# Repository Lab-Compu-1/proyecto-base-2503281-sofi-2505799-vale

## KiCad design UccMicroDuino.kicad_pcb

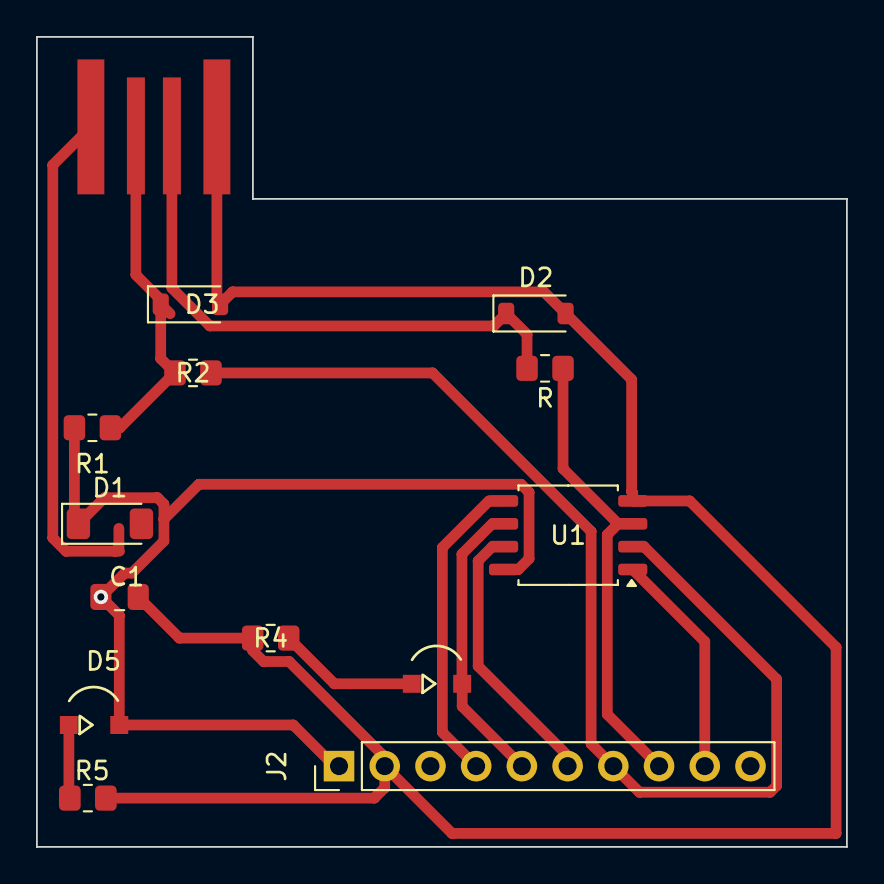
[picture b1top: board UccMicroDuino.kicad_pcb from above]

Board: 2 copper layers, 45.0 x 45.0 mm, 14 parts (0 on the bottom side), 10 nets.

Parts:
C1: C; C_0805_2012Metric_Pad1.18x1.45mm_HandSolder
D1: D_Filled; D_MiniMELF
D2: 3.6V 1/2mw; D_SOD-123
D3: D; D_SOD-123
D5: LED; ledSMD
J1: Pcb USB type A; USB_A_UCC
J2: Header; PinHeader_1x10_P2.54mm_Vertical
R, R2: R; R_0805_2012Metric_Pad1.20x1.40mm_HandSolder
R1: 1/5KΩ 5% 1/8W; R_0805_2012Metric_Pad1.20x1.40mm_HandSolder
R3: Led green; ledSMD
R4, R5: 330Ω 5% 1/8W; R_0805_2012Metric_Pad1.20x1.40mm_HandSolder
U1: ATtiny85-20S; SOIC-8_5.3x5.3mm_P1.27mm

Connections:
+5V: C1.1, D1.1 (K), D2.1 (K), D3.1 (K), D5.2 (A), J1.2 (D-), J1.3 (D+), J2.1, R.2, R1.1, R1.2, R2.2, U1.8 (VCC)
GND: C1.2, D2.2 (A), D3.2 (A), J1.4 (GND), J2.2, R4.1, R5.2, U1.4 (GND)
unnamed: J2.5, R3.2 (A), U1.6 (PB1)
unnamed: R3.1 (K), R4.2
unnamed: D5.1 (K), R5.1
unnamed: J2.4, U1.5 (AREF/PB0)
unnamed: J2.6, U1.7 (PB2)
unnamed: J2.7, R2.1, U1.2 (XTAL1/PB3)
unnamed: J2.8, R.1, U1.3 (XTAL2/PB4)
unnamed: J2.9, U1.1 (~RESET/PB5)

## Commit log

2025-04-07 GitHub Classroom Feedback
2025-04-07 Setting up GitHub Classroom Feedback
